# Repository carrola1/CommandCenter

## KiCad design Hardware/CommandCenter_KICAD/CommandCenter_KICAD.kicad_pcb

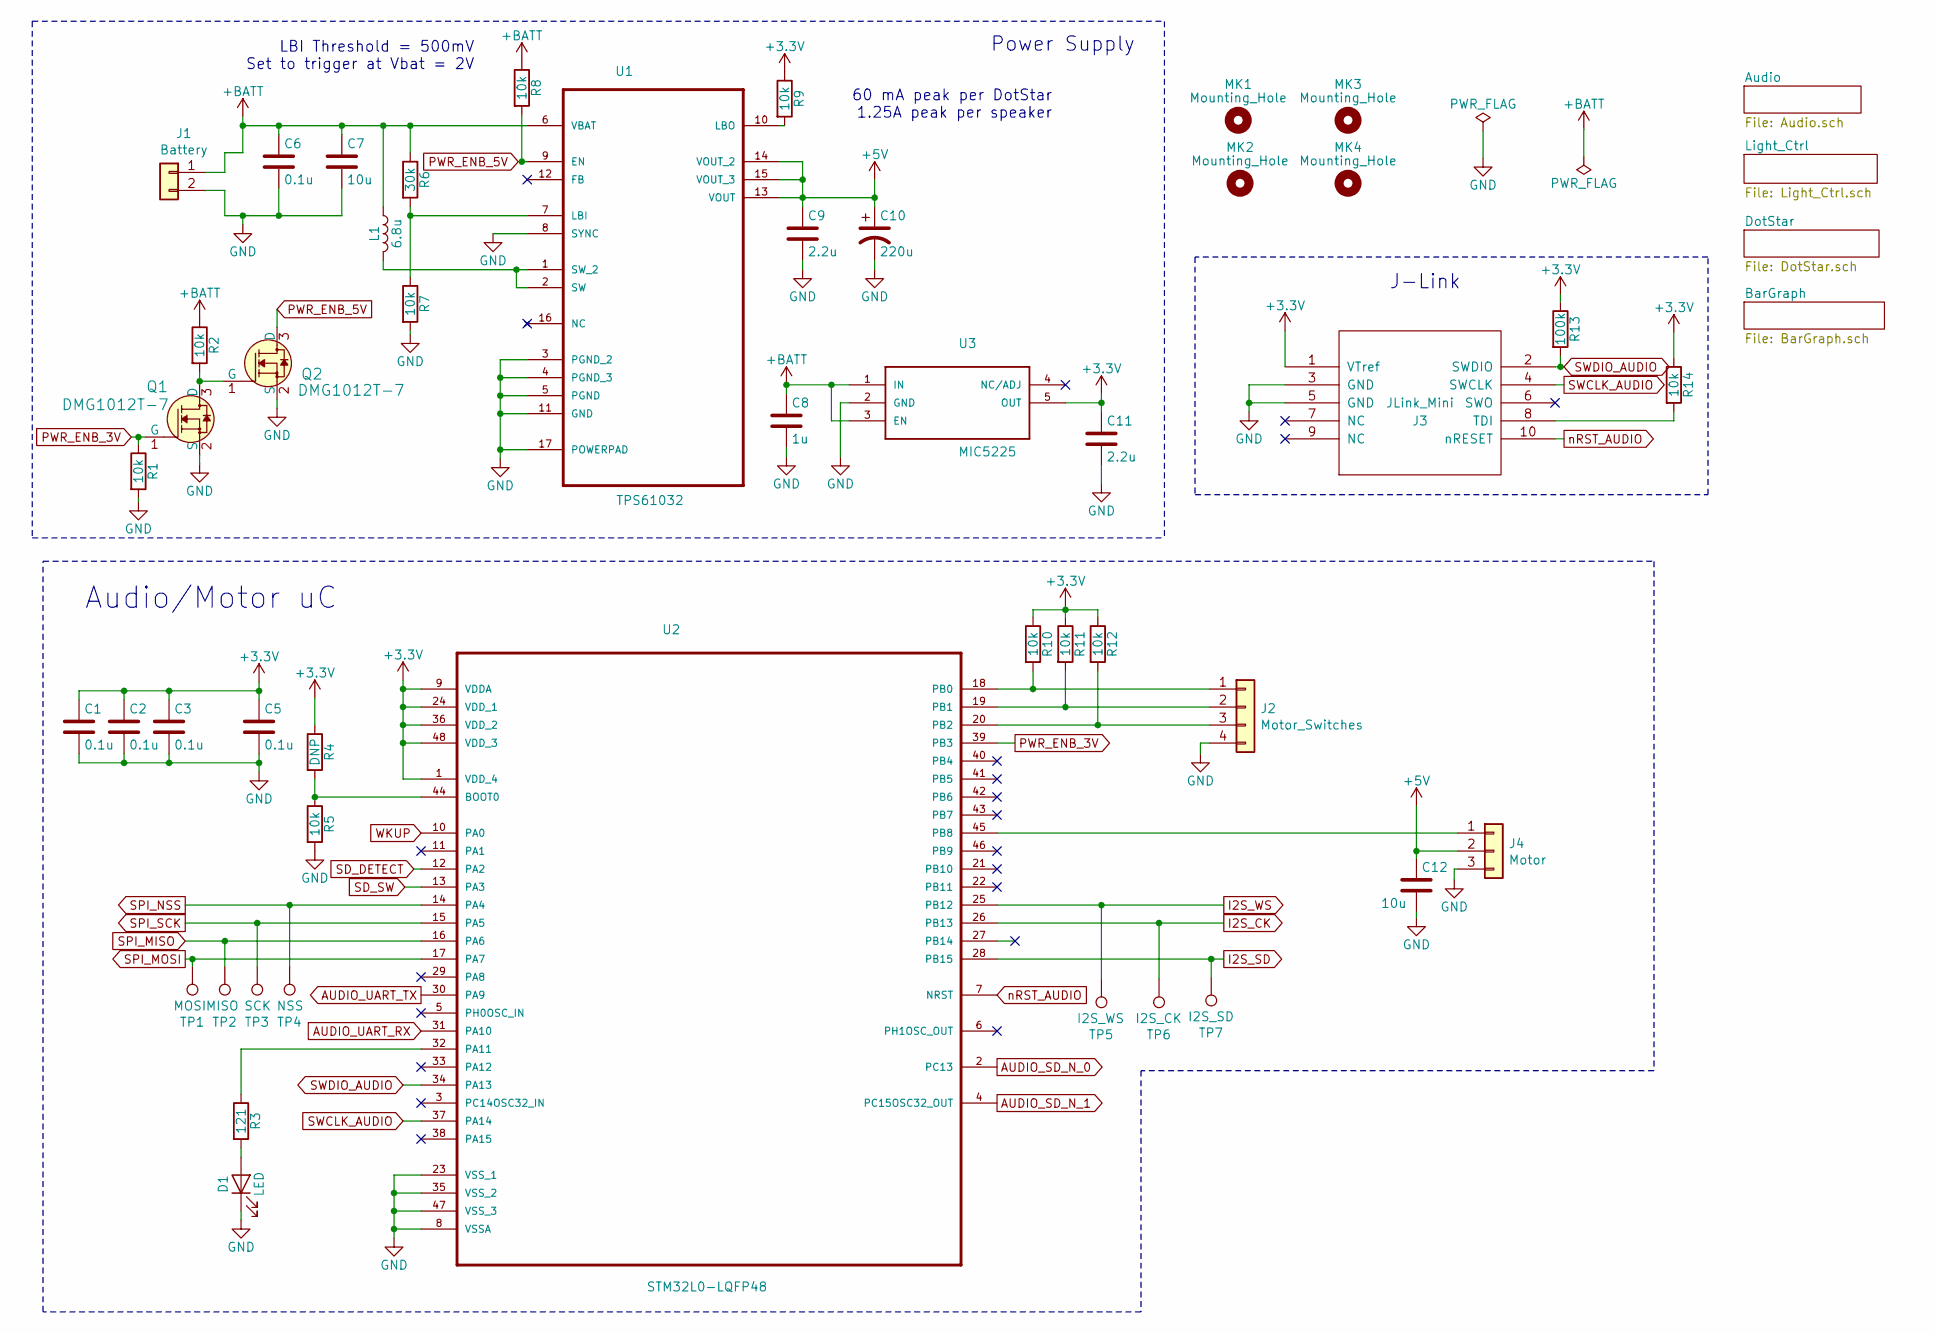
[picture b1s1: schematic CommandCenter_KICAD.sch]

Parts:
C1, C2, C3, C5: 0.1u; C_0603_1608Metric_Pad1.05x0.95mm_HandSolder
C6: 0.1u; C_0402_1005Metric
C7, C12: 10u; C_0603_1608Metric_Pad1.05x0.95mm_HandSolder
C8: 1u; C_0603_1608Metric_Pad1.05x0.95mm_HandSolder
C9, C11: 2.2u; C_0603_1608Metric_Pad1.05x0.95mm_HandSolder
C10: 220u; C_1206_3216Metric_Pad1.42x1.75mm_HandSolder
D1: LED; LED_0603_1608Metric_Pad1.05x0.95mm_HandSolder
J1: Battery; JST_PH_S2B-PH-K_1x02_P2.00mm_Horizontal
J2: Motor_Switches; PinHeader_1x04_P2.54mm_Vertical
J3: JLink_Mini; JLink_Mini_0p05
J4: Motor; PinHeader_1x03_P2.54mm_Vertical
L1: 6.8u; L_12x12mm_H4.5mm
MK1, MK2, MK3, MK4: Mounting_Hole; MountingHole_3.2mm_M3
Q1, Q2: DMG1012T-7; SOT-523; MPN DMG1012T-7; Digi-Key_PN DMG1012T-7DICT-ND
R1, R2, R5, R7, R8, R9, R10, R11, R12, R14: 10k; R_0603_1608Metric_Pad1.05x0.95mm_HandSolder
R3: 121; R_0603_1608Metric_Pad1.05x0.95mm_HandSolder
R4: DNP; R_0603_1608Metric_Pad1.05x0.95mm_HandSolder
R6: 30k; R_0603_1608Metric_Pad1.05x0.95mm_HandSolder
R13: 100k; R_0603_1608Metric_Pad1.05x0.95mm_HandSolder
TP1: MOSI; TestPoint_Pad_2.0x2.0mm
TP2: MISO; TestPoint_Pad_2.0x2.0mm
TP3: SCK; TestPoint_Pad_2.0x2.0mm
TP4: NSS; TestPoint_Pad_2.0x2.0mm
TP5: I2S_WS; TestPoint_Pad_2.0x2.0mm
TP6: I2S_CK; TestPoint_Pad_2.0x2.0mm
TP7: I2S_SD; TestPoint_Pad_2.0x2.0mm
U1: TPS61032; SOP65P640X120-17N
U2: STM32L0-LQFP48; QFP50P900X900X160-48N
U3: MIC5225; SOT-23-5

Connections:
+3V3: C1.1, C2.1, C3.1, C5.1, C11.1, J3.1 (VTref), R4.1, R9.1, R10.1, R11.1, R12.1, R13.1, R14.1, U2.1 (VDD_4), U2.9 (VDDA), U2.24 (VDD_1), U2.36 (VDD_2), U2.48 (VDD_3), U3.5 (OUT); also elsewhere on the board
+5V: C9.1, C10.1, C12.1, J4.2, U1.13 (VOUT), U1.14 (VOUT_2), U1.15 (VOUT_3); also elsewhere on the board
+BATT: C6.1, C7.1, C8.1, J1.1, L1.1, R2.1, R6.1, R8.1, U1.6 (VBAT), U3.1 (IN), U3.3 (EN)
AUDIO_SD_N_0: U2.2 (PC13); also elsewhere on the board
AUDIO_SD_N_1: U2.4 (PC15OSC32_OUT); also elsewhere on the board
AUDIO_UART_RX: U2.31 (PA10); also elsewhere on the board
AUDIO_UART_TX: U2.30 (PA9); also elsewhere on the board
GND: C1.2, C2.2, C3.2, C5.2, C6.2, C7.2, C8.2, C9.2, C10.2, C11.2, C12.2, D1.1 (K), J1.2, J2.4, J3.3 (GND), J3.5 (GND), J4.3, Q1.2 (S), Q2.2 (S), R1.2, R5.2, R7.2, U1.3 (PGND_2), U1.4 (PGND_3), U1.5 (PGND), U1.8 (SYNC), U1.11 (GND), U1.17 (POWERPAD), U2.8 (VSSA), U2.23 (VSS_1), U2.35 (VSS_2), U2.47 (VSS_3), U3.2 (GND); also elsewhere on the board
I2S_CK: TP6.1, U2.26 (PB13); also elsewhere on the board
I2S_SD: TP7.1, U2.28 (PB15); also elsewhere on the board
I2S_WS: TP5.1, U2.25 (PB12); also elsewhere on the board
unnamed: D1.2 (A), R3.2
unnamed: J2.1, R10.2, U2.18 (PB0)
unnamed: J2.2, R11.2, U2.19 (PB1)
unnamed: J2.3, R12.2, U2.20 (PB2)
unnamed: J3.8 (TDI), R14.2
unnamed: J4.1, U2.45 (PB8)
unnamed: L1.2, U1.1 (SW_2), U1.2 (SW)
unnamed: Q1.3 (D), Q2.1 (G), R2.2
unnamed: R3.1, U2.32 (PA11)
unnamed: R4.2, R5.1, U2.44 (BOOT0)
unnamed: R6.2, R7.1, U1.7 (LBI)
unnamed: R9.2, U1.10 (LBO)
PWR_ENB_3V: Q1.1 (G), R1.1, U2.39 (PB3)
PWR_ENB_5V: Q2.3 (D), R8.2, U1.9 (EN)
SD_DETECT: U2.12 (PA2); also elsewhere on the board
SD_SW: U2.13 (PA3); also elsewhere on the board
SPI_MISO: TP2.1, U2.16 (PA6); also elsewhere on the board
SPI_MOSI: TP1.1, U2.17 (PA7); also elsewhere on the board
SPI_NSS: TP4.1, U2.14 (PA4); also elsewhere on the board
SPI_SCK: TP3.1, U2.15 (PA5); also elsewhere on the board
SWCLK_AUDIO: J3.4 (SWCLK), U2.37 (PA14)
SWDIO_AUDIO: J3.2 (SWDIO), R13.2, U2.34 (PA13)
WKUP: U2.10 (PA0); also elsewhere on the board
nRST_AUDIO: J3.10 (nRESET), U2.7 (NRST)

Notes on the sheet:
Power Supply
J-Link
Audio/Motor uC
60 mA peak per DotStar 1.25A peak per speaker
LBI Threshold = 500mV Set to trigger at Vbat = 2V

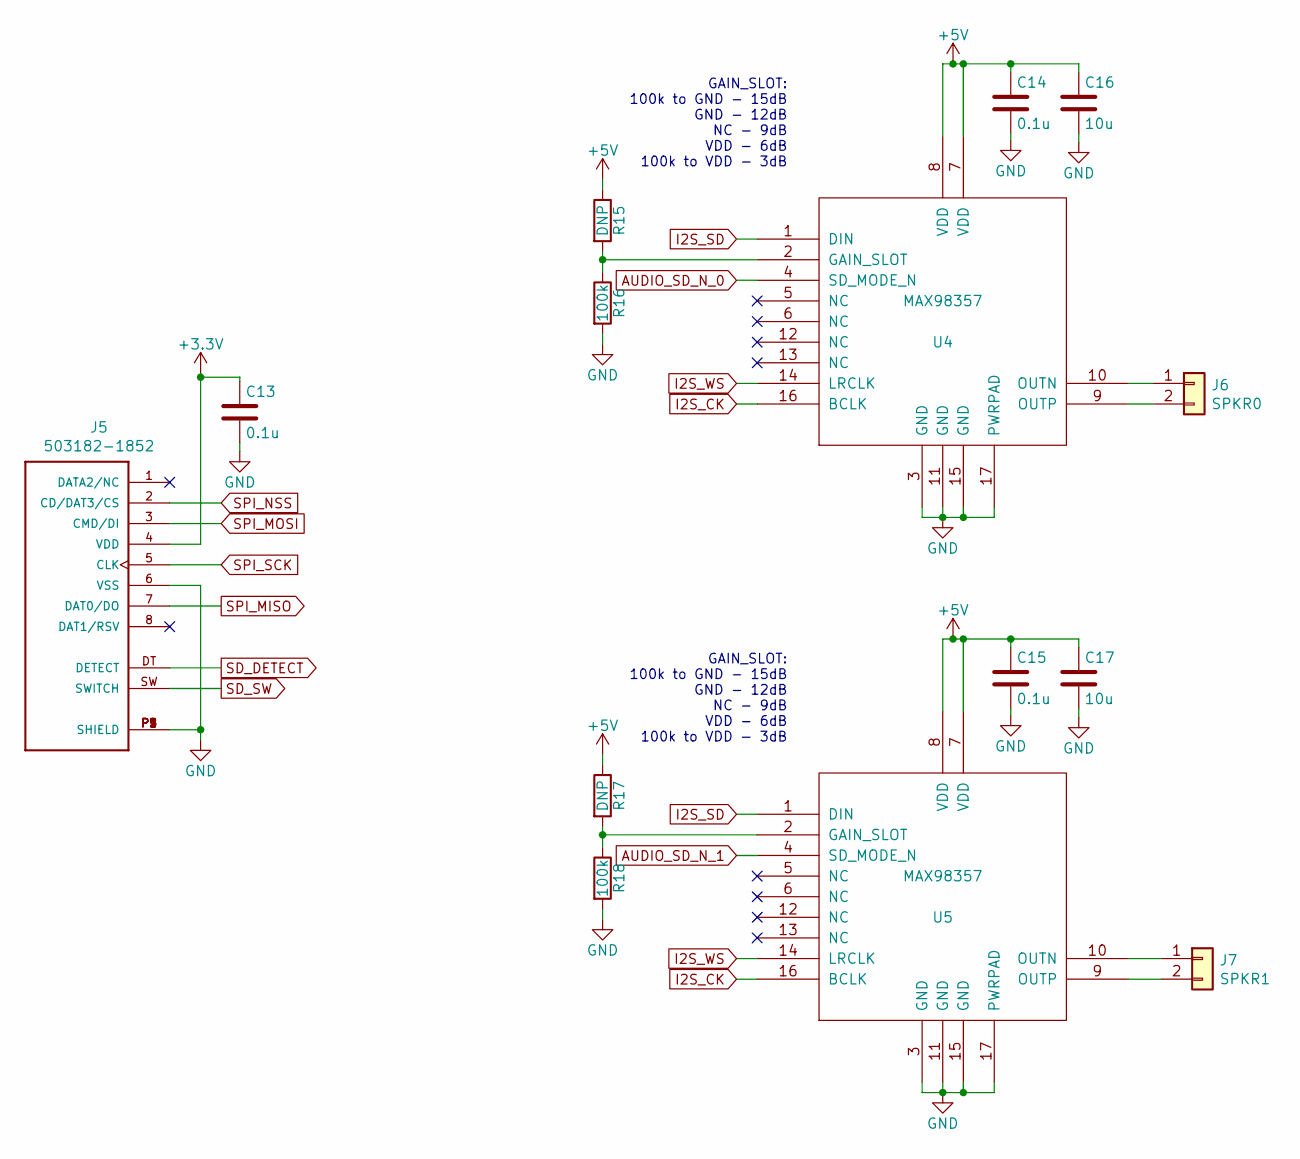
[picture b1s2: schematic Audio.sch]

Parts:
C13, C14, C15: 0.1u; C_0603_1608Metric_Pad1.05x0.95mm_HandSolder
C16, C17: 10u; C_0603_1608Metric_Pad1.05x0.95mm_HandSolder
J5: 503182-1852; MOLEX_503182-1852
J6: SPKR0; PinHeader_1x02_P2.54mm_Vertical
J7: SPKR1; PinHeader_1x02_P2.54mm_Vertical
R15, R17: DNP; R_0603_1608Metric_Pad1.05x0.95mm_HandSolder
R16, R18: 100k; R_0603_1608Metric_Pad1.05x0.95mm_HandSolder
U4, U5: MAX98357; QFN50P300X300X80-17N

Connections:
+3V3: C13.1, J5.4 (VDD); also elsewhere on the board
+5V: C14.1, C15.1, C16.1, C17.1, R15.1, R17.1, U4.7 (VDD), U4.8 (VDD), U5.7 (VDD), U5.8 (VDD); also elsewhere on the board
AUDIO_SD_N_0: U4.4 (SD_MODE_N); also elsewhere on the board
AUDIO_SD_N_1: U5.4 (SD_MODE_N); also elsewhere on the board
GND: C13.2, C14.2, C15.2, C16.2, C17.2, J5.6 (VSS), J5.P1 (SHIELD), J5.P2 (SHIELD), J5.P3 (SHIELD), J5.P4 (SHIELD), J5.P5 (SHIELD), R16.2, R18.2, U4.3 (GND), U4.11 (GND), U4.15 (GND), U4.17 (PWRPAD), U5.3 (GND), U5.11 (GND), U5.15 (GND), U5.17 (PWRPAD); also elsewhere on the board
I2S_CK: U4.16 (BCLK), U5.16 (BCLK); also elsewhere on the board
I2S_SD: U4.1 (DIN), U5.1 (DIN); also elsewhere on the board
I2S_WS: U4.14 (LRCLK), U5.14 (LRCLK); also elsewhere on the board
unnamed: J6.1, U4.10 (OUTN)
unnamed: J6.2, U4.9 (OUTP)
unnamed: J7.1, U5.10 (OUTN)
unnamed: J7.2, U5.9 (OUTP)
unnamed: R15.2, R16.1, U4.2 (GAIN_SLOT)
unnamed: R17.2, R18.1, U5.2 (GAIN_SLOT)
SD_DETECT: J5.DT (DETECT); also elsewhere on the board
SD_SW: J5.SW (SWITCH); also elsewhere on the board
SPI_MISO: J5.7 (DAT0/DO); also elsewhere on the board
SPI_MOSI: J5.3 (CMD/DI); also elsewhere on the board
SPI_NSS: J5.2 (CD/DAT3/CS); also elsewhere on the board
SPI_SCK: J5.5 (CLK); also elsewhere on the board

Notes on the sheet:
GAIN_SLOT: 100k to GND - 15dB GND - 12dB NC - 9dB VDD - 6dB 100k to VDD - 3dB

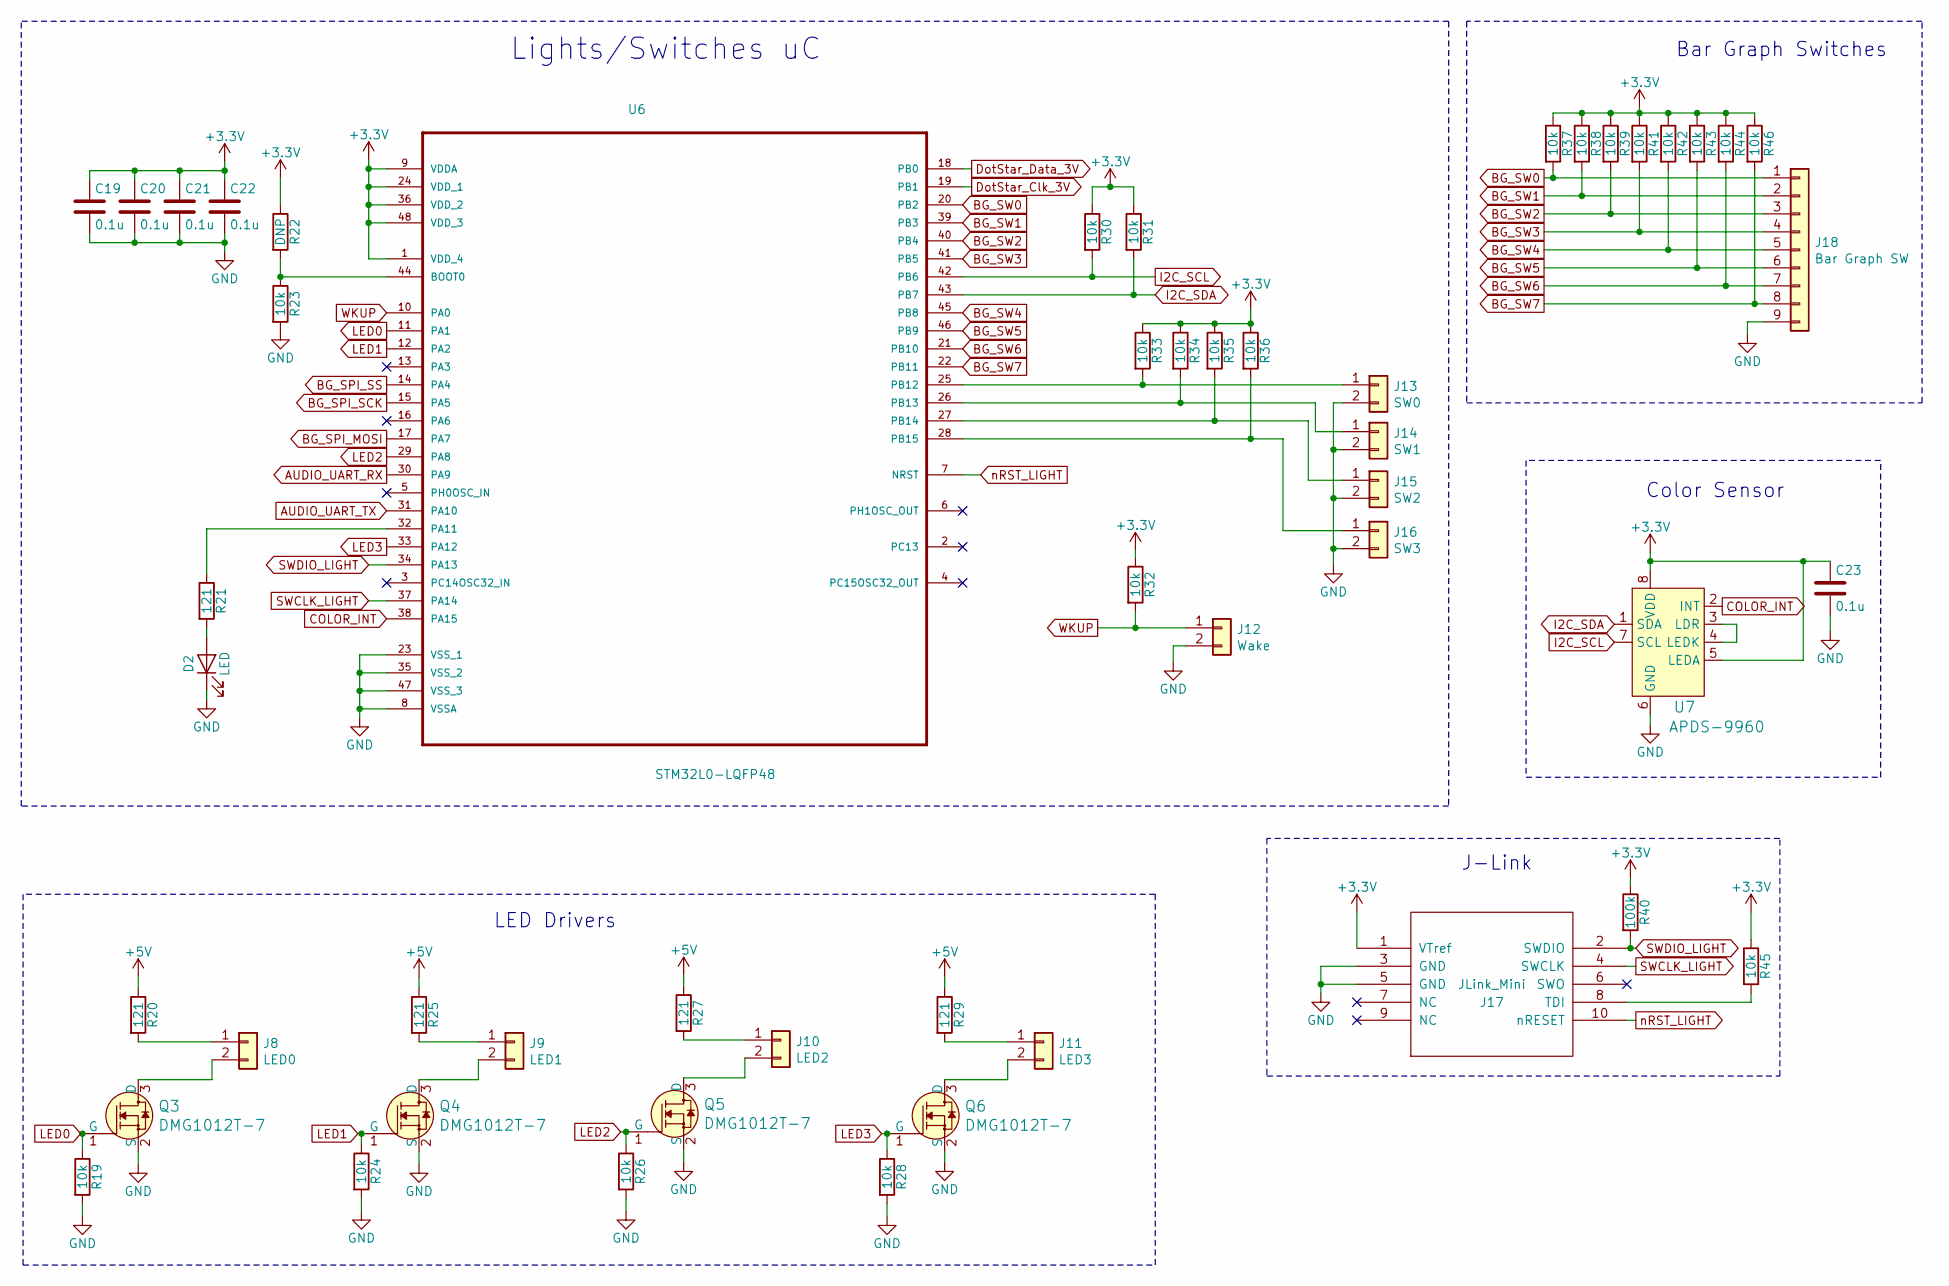
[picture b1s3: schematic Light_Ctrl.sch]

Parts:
C19, C20, C21, C22, C23: 0.1u; C_0603_1608Metric_Pad1.05x0.95mm_HandSolder
D2: LED; LED_0603_1608Metric_Pad1.05x0.95mm_HandSolder
J8: LED0; PinHeader_1x02_P2.54mm_Vertical
J9: LED1; PinHeader_1x02_P2.54mm_Vertical
J10: LED2; PinHeader_1x02_P2.54mm_Vertical
J11: LED3; PinHeader_1x02_P2.54mm_Vertical
J12: Wake; PinHeader_1x02_P2.54mm_Vertical
J13: SW0; PinHeader_1x02_P2.54mm_Vertical
J14: SW1; PinHeader_1x02_P2.54mm_Vertical
J15: SW2; PinHeader_1x02_P2.54mm_Vertical
J16: SW3; PinHeader_1x02_P2.54mm_Vertical
J17: JLink_Mini; JLink_Mini_0p05
J18: Bar Graph SW; PinHeader_1x09_P2.54mm_Vertical
Q3, Q4, Q5, Q6: DMG1012T-7; SOT-523; MPN DMG1012T-7; Digi-Key_PN DMG1012T-7DICT-ND
R19, R23, R24, R26, R28, R30, R31, R32, R33, R34, R35, R36, R37, R38, R39, R41, R42, R43, R44, R45, R46: 10k; R_0603_1608Metric_Pad1.05x0.95mm_HandSolder
R20, R21, R25, R27, R29: 121; R_0603_1608Metric_Pad1.05x0.95mm_HandSolder
R22: DNP; R_0603_1608Metric_Pad1.05x0.95mm_HandSolder
R40: 100k; R_0603_1608Metric_Pad1.05x0.95mm_HandSolder
U6: STM32L0-LQFP48; QFP50P900X900X160-48N
U7: APDS-9960; Ambient_Prox_APDS-9960; MPN APDS-9960; Digi-Key_PN 516-3480-1-ND

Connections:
+3V3: C19.1, C20.1, C21.1, C22.1, C23.1, J17.1 (VTref), R22.1, R30.1, R31.1, R32.1, R33.1, R34.1, R35.1, R36.1, R37.1, R38.1, R39.1, R40.1, R41.1, R42.1, R43.1, R44.1, R45.1, R46.1, U6.1 (VDD_4), U6.9 (VDDA), U6.24 (VDD_1), U6.36 (VDD_2), U6.48 (VDD_3), U7.5 (LEDA), U7.8 (VDD); also elsewhere on the board
+5V: R20.1, R25.1, R27.1, R29.1; also elsewhere on the board
AUDIO_UART_RX: U6.30 (PA9); also elsewhere on the board
AUDIO_UART_TX: U6.31 (PA10); also elsewhere on the board
BG_SPI_MOSI: U6.17 (PA7); also elsewhere on the board
BG_SPI_SCK: U6.15 (PA5); also elsewhere on the board
BG_SPI_SS: U6.14 (PA4); also elsewhere on the board
BG_SW0: J18.1, R37.2, U6.20 (PB2)
BG_SW1: J18.2, R38.2, U6.39 (PB3)
BG_SW2: J18.3, R39.2, U6.40 (PB4)
BG_SW3: J18.4, R41.2, U6.41 (PB5)
BG_SW4: J18.5, R42.2, U6.45 (PB8)
BG_SW5: J18.6, R43.2, U6.46 (PB9)
BG_SW6: J18.7, R44.2, U6.21 (PB10)
BG_SW7: J18.8, R46.2, U6.22 (PB11)
COLOR_INT: U6.38 (PA15), U7.2 (INT)
DotStar_Clk_3V: U6.19 (PB1); also elsewhere on the board
DotStar_Data_3V: U6.18 (PB0); also elsewhere on the board
GND: C19.2, C20.2, C21.2, C22.2, C23.2, D2.1 (K), J12.2, J13.2, J14.2, J15.2, J16.2, J17.3 (GND), J17.5 (GND), J18.9, Q3.2 (S), Q4.2 (S), Q5.2 (S), Q6.2 (S), R19.2, R23.2, R24.2, R26.2, R28.2, U6.8 (VSSA), U6.23 (VSS_1), U6.35 (VSS_2), U6.47 (VSS_3), U7.6 (GND); also elsewhere on the board
I2C_SCL: R30.2, U6.42 (PB6), U7.7 (SCL)
I2C_SDA: R31.2, U6.43 (PB7), U7.1 (SDA)
LED0: Q3.1 (G), R19.1, U6.11 (PA1)
LED1: Q4.1 (G), R24.1, U6.12 (PA2)
LED2: Q5.1 (G), R26.1, U6.29 (PA8)
LED3: Q6.1 (G), R28.1, U6.33 (PA12)
unnamed: D2.2 (A), R21.2
unnamed: J8.1, R20.2
unnamed: J8.2, Q3.3 (D)
unnamed: J9.1, R25.2
unnamed: J9.2, Q4.3 (D)
unnamed: J10.1, R27.2
unnamed: J10.2, Q5.3 (D)
unnamed: J11.1, R29.2
unnamed: J11.2, Q6.3 (D)
unnamed: J13.1, R33.2, U6.25 (PB12)
unnamed: J14.1, R34.2, U6.26 (PB13)
unnamed: J15.1, R35.2, U6.27 (PB14)
unnamed: J16.1, R36.2, U6.28 (PB15)
unnamed: J17.8 (TDI), R45.2
unnamed: R21.1, U6.32 (PA11)
unnamed: R22.2, R23.1, U6.44 (BOOT0)
unnamed: U7.3 (LDR), U7.4 (LEDK)
SWCLK_LIGHT: J17.4 (SWCLK), U6.37 (PA14)
SWDIO_LIGHT: J17.2 (SWDIO), R40.2, U6.34 (PA13)
WKUP: J12.1, R32.2, U6.10 (PA0); also elsewhere on the board
nRST_LIGHT: J17.10 (nRESET), U6.7 (NRST)

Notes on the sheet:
Lights/Switches uC
J-Link
LED Drivers
Color Sensor
Bar Graph Switches

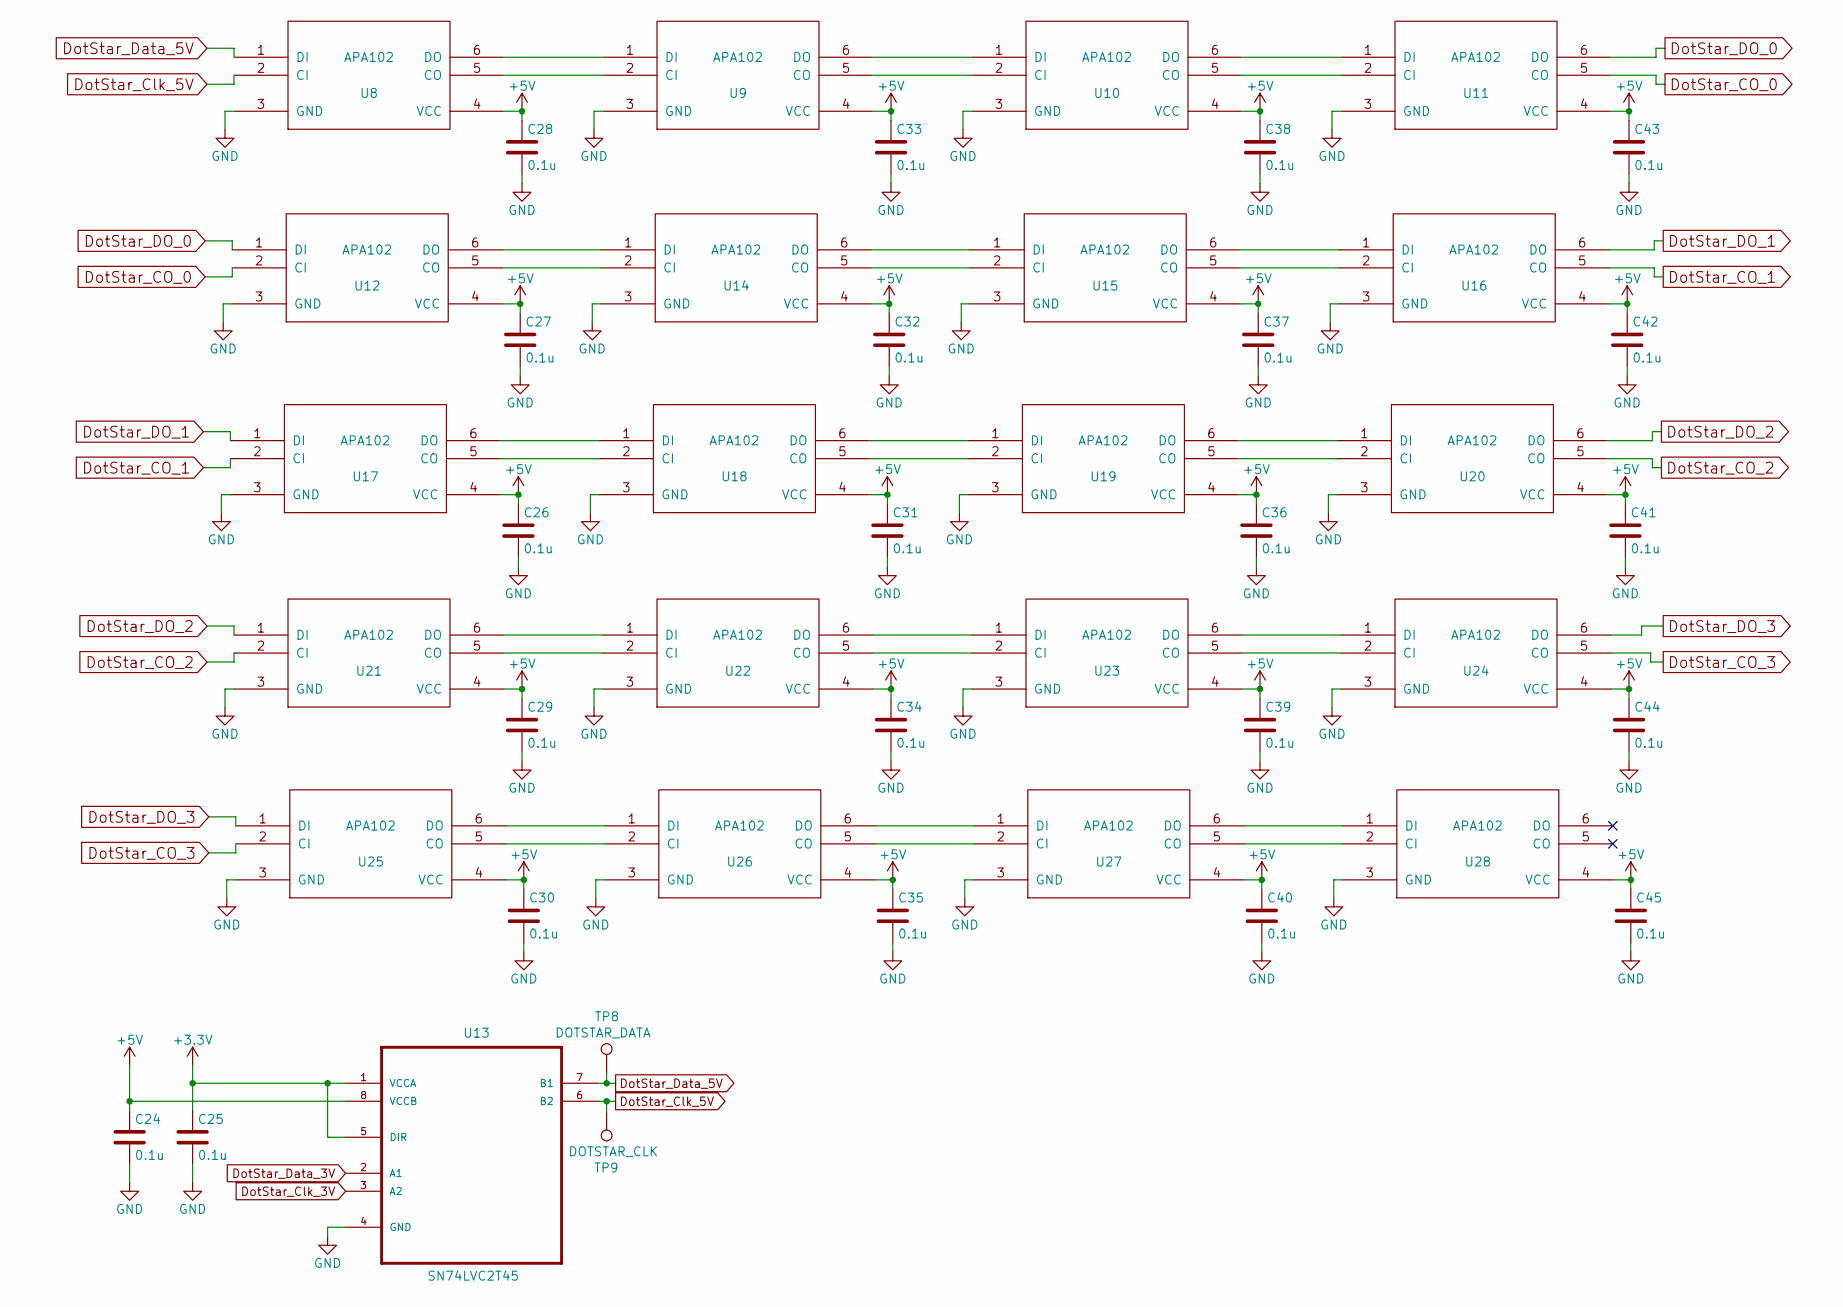
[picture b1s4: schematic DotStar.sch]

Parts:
C24, C25, C26, C27, C28, C29, C30, C31, C32, C33, C34, C35, C36, C37, C38, C39, C40, C41, C42, C43, C44, C45: 0.1u; C_0603_1608Metric_Pad1.05x0.95mm_HandSolder
TP8: DOTSTAR_DATA; TestPoint_Pad_2.0x2.0mm
TP9: DOTSTAR_CLK; TestPoint_Pad_2.0x2.0mm
U8, U9, U10, U11, U12, U14, U15, U16, U17, U18, U19, U20, U21, U22, U23, U24, U25, U26, U27, U28: APA102; APA102_hand_solder
U13: SN74LVC2T45; SOP50P310X90-8N

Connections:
+3V3: C25.1, U13.1 (VCCA), U13.5 (DIR); also elsewhere on the board
+5V: C24.1, C26.1, C27.1, C28.1, C29.1, C30.1, C31.1, C32.1, C33.1, C34.1, C35.1, C36.1, C37.1, C38.1, C39.1, C40.1, C41.1, C42.1, C43.1, C44.1, C45.1, U8.4 (VCC), U9.4 (VCC), U10.4 (VCC), U11.4 (VCC), U12.4 (VCC), U13.8 (VCCB), U14.4 (VCC), U15.4 (VCC), U16.4 (VCC), U17.4 (VCC), U18.4 (VCC), U19.4 (VCC), U20.4 (VCC), U21.4 (VCC), U22.4 (VCC), U23.4 (VCC), U24.4 (VCC), U25.4 (VCC), U26.4 (VCC), U27.4 (VCC), U28.4 (VCC); also elsewhere on the board
DotStar_CO_0: U11.5 (CO), U12.2 (CI)
DotStar_CO_1: U16.5 (CO), U17.2 (CI)
DotStar_CO_2: U20.5 (CO), U21.2 (CI)
DotStar_CO_3: U24.5 (CO), U25.2 (CI)
DotStar_Clk_3V: U13.3 (A2); also elsewhere on the board
DotStar_Clk_5V: TP9.1, U8.2 (CI), U13.6 (B2)
DotStar_DO_0: U11.6 (DO), U12.1 (DI)
DotStar_DO_1: U16.6 (DO), U17.1 (DI)
DotStar_DO_2: U20.6 (DO), U21.1 (DI)
DotStar_DO_3: U24.6 (DO), U25.1 (DI)
DotStar_Data_3V: U13.2 (A1); also elsewhere on the board
DotStar_Data_5V: TP8.1, U8.1 (DI), U13.7 (B1)
GND: C24.2, C25.2, C26.2, C27.2, C28.2, C29.2, C30.2, C31.2, C32.2, C33.2, C34.2, C35.2, C36.2, C37.2, C38.2, C39.2, C40.2, C41.2, C42.2, C43.2, C44.2, C45.2, U8.3 (GND), U9.3 (GND), U10.3 (GND), U11.3 (GND), U12.3 (GND), U13.4 (GND), U14.3 (GND), U15.3 (GND), U16.3 (GND), U17.3 (GND), U18.3 (GND), U19.3 (GND), U20.3 (GND), U21.3 (GND), U22.3 (GND), U23.3 (GND), U24.3 (GND), U25.3 (GND), U26.3 (GND), U27.3 (GND), U28.3 (GND); also elsewhere on the board
unnamed: U8.5 (CO), U9.2 (CI)
unnamed: U8.6 (DO), U9.1 (DI)
unnamed: U9.6 (DO), U10.1 (DI)
unnamed: U9.5 (CO), U10.2 (CI)
unnamed: U10.5 (CO), U11.2 (CI)
unnamed: U10.6 (DO), U11.1 (DI)
unnamed: U12.5 (CO), U14.2 (CI)
unnamed: U12.6 (DO), U14.1 (DI)
unnamed: U14.5 (CO), U15.2 (CI)
unnamed: U14.6 (DO), U15.1 (DI)
unnamed: U15.5 (CO), U16.2 (CI)
unnamed: U15.6 (DO), U16.1 (DI)
unnamed: U17.5 (CO), U18.2 (CI)
unnamed: U17.6 (DO), U18.1 (DI)
unnamed: U18.5 (CO), U19.2 (CI)
unnamed: U18.6 (DO), U19.1 (DI)
unnamed: U19.5 (CO), U20.2 (CI)
unnamed: U19.6 (DO), U20.1 (DI)
unnamed: U21.5 (CO), U22.2 (CI)
unnamed: U21.6 (DO), U22.1 (DI)
unnamed: U22.5 (CO), U23.2 (CI)
unnamed: U22.6 (DO), U23.1 (DI)
unnamed: U23.5 (CO), U24.2 (CI)
unnamed: U23.6 (DO), U24.1 (DI)
unnamed: U25.5 (CO), U26.2 (CI)
unnamed: U25.6 (DO), U26.1 (DI)
unnamed: U26.5 (CO), U27.2 (CI)
unnamed: U26.6 (DO), U27.1 (DI)
unnamed: U27.5 (CO), U28.2 (CI)
unnamed: U27.6 (DO), U28.1 (DI)

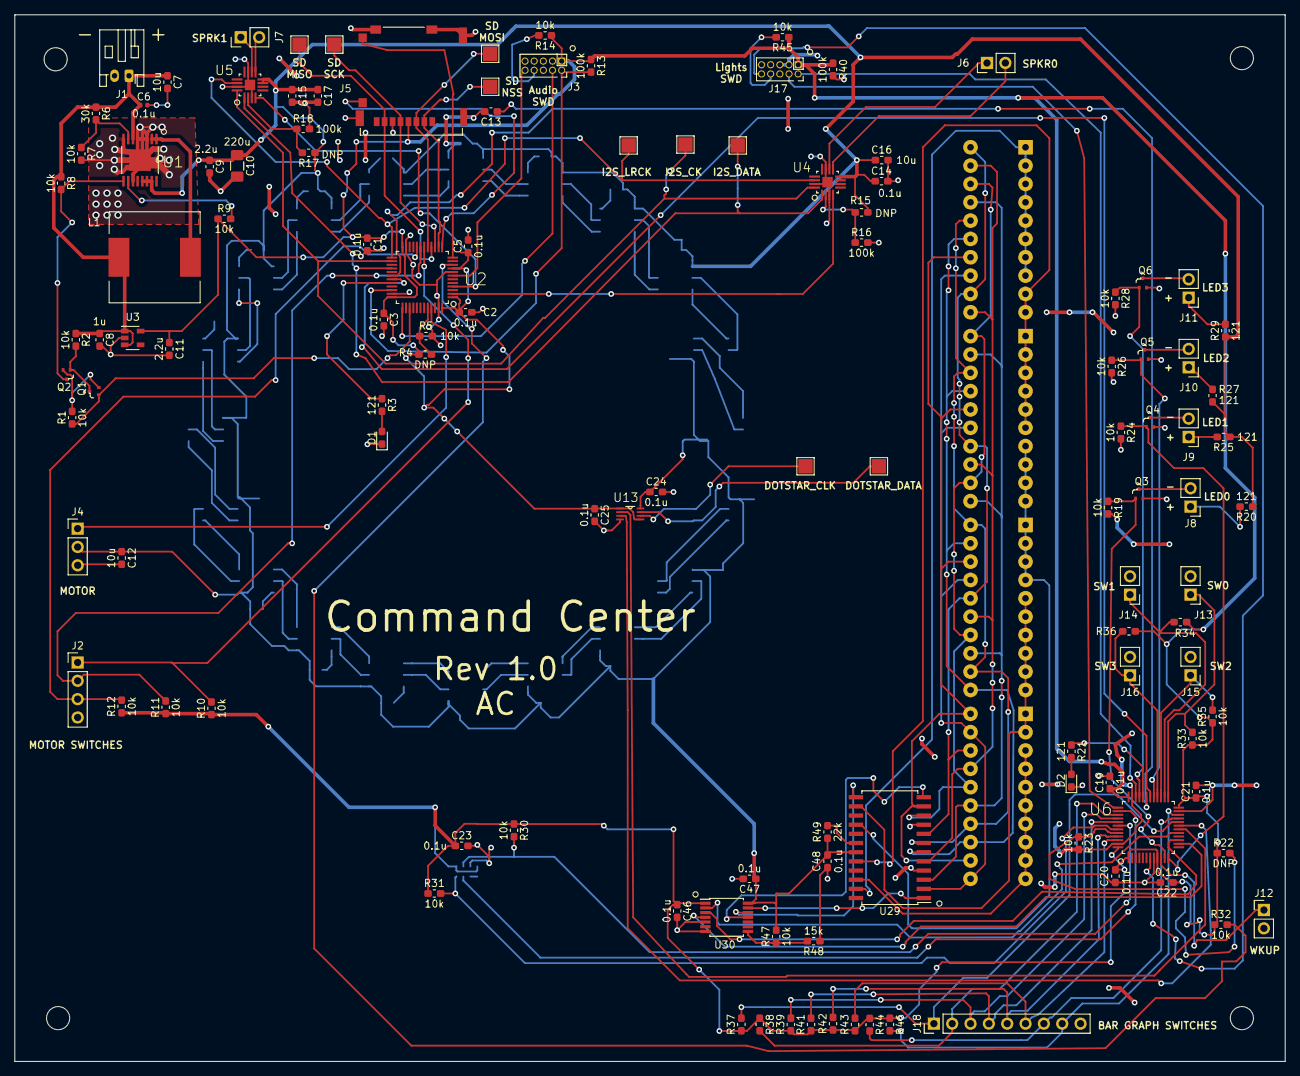
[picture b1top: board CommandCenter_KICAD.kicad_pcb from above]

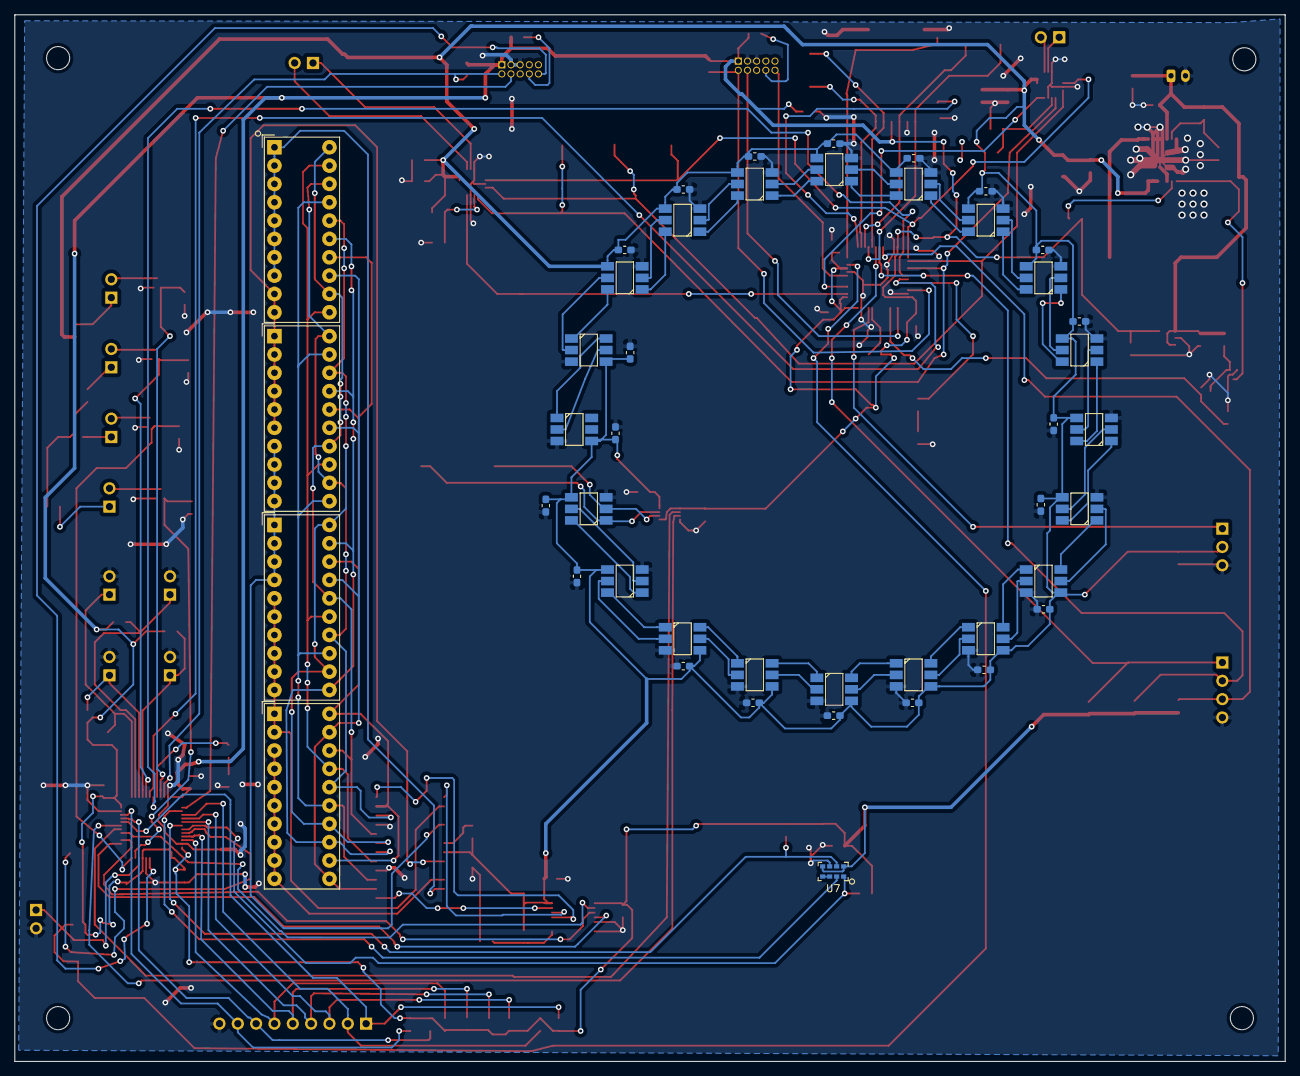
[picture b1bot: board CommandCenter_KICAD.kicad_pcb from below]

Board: 2 copper layers, 176.0 x 145.0 mm, 169 parts (45 on the bottom side), 139 nets.

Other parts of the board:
BAR1, BAR2, BAR3, BAR4: HDSP-4830_2; HDSP-4830
C46, C47, C48: 0.1u; C_0603_1608Metric_Pad1.05x0.95mm_HandSolder
MKe: Mounting_Hole; MountingHole_3.2mm_M3
R47: 10k; R_0603_1608Metric_Pad1.05x0.95mm_HandSolder
R48: 15k; R_0603_1608Metric_Pad1.05x0.95mm_HandSolder
R49: 22k; R_0603_1608Metric_Pad1.05x0.95mm_HandSolder
U29: MAX7219; SOIC-24W_7.5x15.4mm_P1.27mm
U30: TXB0104PW; TSSOP-14_4.4x5mm_P0.65mm

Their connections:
+3V3: C46.1, U30.1; also elsewhere on the board
+5V: C47.1, C48.1, R47.2, R49.1, U29.19, U30.14; also elsewhere on the board
BG_SPI_MOSI: U30.2; also elsewhere on the board
BG_SPI_MOSI_5V: U29.1, U30.13
BG_SPI_SCK: U30.3; also elsewhere on the board
BG_SPI_SCK_5V: U29.13, U30.12
BG_SPI_SS: U30.4; also elsewhere on the board
BG_SPI_SS_5V: U29.12, U30.11
DIG0: BAR1.13, BAR2.15, BAR3.17, BAR4.11, BAR4.19, U29.2
DIG1: BAR1.14, BAR2.16, BAR3.18, BAR4.12, BAR4.20, U29.11
DIG2: BAR1.15, BAR2.17, BAR3.11, BAR3.19, BAR4.13, U29.6
DIG3: BAR1.16, BAR2.18, BAR3.12, BAR3.20, BAR4.14, U29.7
DIG4: BAR1.17, BAR2.11, BAR2.19, BAR3.13, BAR4.15, U29.3
DIG5: BAR1.18, BAR2.12, BAR2.20, BAR3.14, BAR4.16, U29.10
DIG6: BAR1.11, BAR1.19, BAR2.13, BAR3.15, BAR4.17, U29.5
DIG7: BAR1.12, BAR1.20, BAR2.14, BAR3.16, BAR4.18, U29.8
GND: C46.2, C47.2, C48.2, R48.1, U29.4, U29.9, U30.5, U30.7; also elsewhere on the board
unnamed: R47.1, R48.2, U30.8
unnamed: R49.2, U29.18
SEG_A: BAR3.5, BAR3.6, BAR3.7, BAR3.8, BAR3.9, BAR3.10, BAR4.1, BAR4.2, U29.14
SEG_B: BAR2.7, BAR2.8, BAR2.9, BAR2.10, BAR3.1, BAR3.2, BAR3.3, BAR3.4, U29.16
SEG_C: BAR1.9, BAR1.10, BAR2.1, BAR2.2, BAR2.3, BAR2.4, BAR2.5, BAR2.6, U29.20
SEG_D: BAR1.1, BAR1.2, BAR1.3, BAR1.4, BAR1.5, BAR1.6, BAR1.7, BAR1.8, U29.23
SEG_DP: BAR4.3, BAR4.4, BAR4.5, BAR4.6, BAR4.7, BAR4.8, BAR4.9, BAR4.10, U29.22

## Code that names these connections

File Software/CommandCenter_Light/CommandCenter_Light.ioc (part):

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Mcu.Name=STM32L052C(6-8)Tx
Mcu.Package=LQFP48
Mcu.UserName=STM32L052C8Tx
PA0.Mode=SYS_WakeUp0
PA0.Signal=SYS_WKUP1
PA1.GPIOParameters=GPIO_Label
PA1.GPIO_Label=LED_0
PA1.Signal=GPIO_Output
PA10.Mode=Asynchronous
PA10.Signal=USART1_RX
PA11.GPIOParameters=GPIO_Label
PA11.GPIO_Label=TEST_LED
PA11.Signal=GPIO_Output
PA12.GPIOParameters=GPIO_Label
PA12.GPIO_Label=LED_3
PA12.Signal=GPIO_Output
PA13.Mode=Serial_Wire
PA13.Signal=SYS_SWDIO
PA14.Mode=Serial_Wire
PA14.Signal=SYS_SWCLK
PA15.GPIOParameters=GPIO_Label
PA15.GPIO_Label=COLOR_INT
PA15.Signal=GPIO_Input
PA2.GPIOParameters=GPIO_Label
PA2.GPIO_Label=LED_1
PA2.Signal=GPIO_Output
PA4.GPIOParameters=PinState,GPIO_Label
PA4.GPIO_Label=SPI_SS
PA4.PinState=GPIO_PIN_SET
PA4.Signal=GPIO_Output
PA5.GPIOParameters=GPIO_PuPd
PA5.GPIO_PuPd=GPIO_NOPULL
PA5.Mode=TX_Only_Simplex_Unidirect_Master
PA5.Signal=SPI1_SCK
PA6.Signal=SPI1_MISO
PA7.GPIOParameters=GPIO_PuPd
PA7.GPIO_PuPd=GPIO_NOPULL
PA7.Mode=TX_Only_Simplex_Unidirect_Master
PA7.Signal=SPI1_MOSI
PA8.GPIOParameters=GPIO_Label
PA8.GPIO_Label=LED_2
PA8.Signal=GPIO_Output
PA9.Mode=Asynchronous
PA9.Signal=USART1_TX
PB0.GPIOParameters=GPIO_Label
PB0.GPIO_Label=DOTSTAR_DATA
PB0.Signal=GPIO_Output
PB1.GPIOParameters=GPIO_Label
PB1.GPIO_Label=DOTSTAR_CLK
PB1.Signal=GPIO_Output
PB10.GPIOParameters=GPIO_Label
PB10.GPIO_Label=BG_SW_6
PB10.Signal=GPIO_Input
PB11.GPIOParameters=GPIO_Label
PB11.GPIO_Label=BG_SW_7
PB11.Signal=GPIO_Input
PB12.GPIOParameters=GPIO_Label
PB12.GPIO_Label=SW_0
PB12.Signal=GPIO_Input
PB13.GPIOParameters=GPIO_Label
PB13.GPIO_Label=SW_1
PB13.Signal=GPIO_Input
PB14.GPIOParameters=GPIO_Label
PB14.GPIO_Label=SW_2
PB14.Signal=GPIO_Input
PB15.GPIOParameters=GPIO_Label
PB15.GPIO_Label=SW_3
PB15.Signal=GPIO_Input
PB2.GPIOParameters=GPIO_Label
PB2.GPIO_Label=BG_SW_0
PB2.Signal=GPIO_Input
PB3.GPIOParameters=GPIO_Label
PB3.GPIO_Label=BG_SW_1
PB3.Signal=GPIO_Input
PB4.GPIOParameters=GPIO_Label
PB4.GPIO_Label=BG_SW_2
PB4.Signal=GPIO_Input
PB5.GPIOParameters=GPIO_Label
PB5.GPIO_Label=BG_SW_3
PB5.Signal=GPIO_Input
PB6.GPIOParameters=GPIO_PuPdOD
PB6.GPIO_PuPdOD=GPIO_NOPULL
PB6.Mode=I2C
PB6.Signal=I2C1_SCL
PB7.Mode=I2C
PB7.Signal=I2C1_SDA
PB8.GPIOParameters=GPIO_Label
PB8.GPIO_Label=BG_SW_4
PB8.Signal=GPIO_Input
PB9.GPIOParameters=GPIO_Label
PB9.GPIO_Label=BG_SW_5
PB9.Signal=GPIO_Input
RCC.HSE_VALUE=8000000
RCC.SYSCLKFreq_VALUE=32000000
RCC.SYSCLKSource=RCC_SYSCLKSOURCE_PLLCLK
board=custom

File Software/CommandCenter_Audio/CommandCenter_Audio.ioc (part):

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Mcu.Name=STM32L052C(6-8)Tx
Mcu.Package=LQFP48
Mcu.UserName=STM32L052C8Tx
PA0.Mode=SYS_WakeUp0
PA0.Signal=SYS_WKUP1
PA10.Mode=Asynchronous
PA10.Signal=USART1_RX
PA11.GPIOParameters=GPIO_Label
PA11.GPIO_Label=TEST_LED
PA11.Signal=GPIO_Output
PA13.Mode=Serial_Wire
PA13.Signal=SYS_SWDIO
PA14.Mode=Serial_Wire
PA14.Signal=SYS_SWCLK
PA2.GPIOParameters=GPIO_Label
PA2.GPIO_Label=SD_DETECT
PA2.Signal=GPIO_Input
PA3.GPIOParameters=GPIO_Label
PA3.GPIO_Label=SD_SW
PA3.Signal=GPIO_Input
PA4.Signal=SPI1_NSS
PA5.Mode=Full_Duplex_Master
PA5.Signal=SPI1_SCK
PA6.Mode=Full_Duplex_Master
PA6.Signal=SPI1_MISO
PA7.Mode=Full_Duplex_Master
PA7.Signal=SPI1_MOSI
PA9.Mode=Asynchronous
PA9.Signal=USART1_TX
PB0.GPIOParameters=GPIO_Label
PB0.GPIO_Label=MOTOR_SW_0
PB0.Signal=GPIO_Input
PB1.GPIOParameters=GPIO_Label
PB1.GPIO_Label=MOTOR_SW_1
PB1.Signal=GPIO_Input
PB12.Mode=Half_Duplex_Master
PB12.Signal=I2S2_WS
PB13.Mode=Half_Duplex_Master
PB13.Signal=I2S2_CK
PB15.Mode=Half_Duplex_Master
PB15.Signal=I2S2_SD
PB2.GPIOParameters=GPIO_Label
PB2.GPIO_Label=MOTOR_CTRL
PB2.Mode=WaveformGeneration
PB2.Signal=LPTIM1_OUT
PB3.GPIOParameters=GPIO_Label
PB3.GPIO_Label=PWR_ENB
PB3.Signal=GPIO_Output
PB8.GPIOParameters=GPIO_Label
PB8.GPIO_Label=MOTOR_SW_2
PB8.Signal=GPIO_Input
PC13.GPIOParameters=GPIO_Label
PC13.GPIO_Label=AUDIO_SD_N_0
PC13.Signal=GPIO_Output
PC15-OSC32_OUT.GPIOParameters=GPIO_Label
PC15-OSC32_OUT.GPIO_Label=AUDIO_SD_N_1
PC15-OSC32_OUT.Signal=GPIO_Output
RCC.HSE_VALUE=8000000
RCC.SYSCLKFreq_VALUE=32000000
RCC.SYSCLKSource=RCC_SYSCLKSOURCE_PLLCLK
board=custom

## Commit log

2019-04-29 Started PCB Schematic
2019-05-12 Layout started
2019-08-28 Light Project Stable
    DotStars and bar graph working. Getting master read nack on I2C to color sensor.
2019-09-02 Bar graph and color sensor working
2019-09-11 Audio project working again
    Had to recreate STM32IDE project to get code to load. Not sure what fixed it. Audio amps were not initially working. Fixed by changing compile optimization from "None" to "Optimize for Size". This wa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
2019-10-16 Servo motor functioning.
2019-10-23 Progress toward final implementation
2019-10-23 UART Working
2019-10-28 All hardware functional
    Sounds added for switch inputs.
2019-12-28 Adding color detection and new audio files.
2019-12-28 Added color detect filtering and RNG for asking to find a random color.
2019-12-28 Added color found success/fail with audio triggers.
2019-12-31 Wake/sleep key switch functionality added.
2020-01-03 Minor timing changes.
2020-01-03 Audio controller now provides UART feedback for when audio is playing
2020-01-03 Final release before mounting
2020-01-06 Added calibration routine on startup
2020-01-07 Fixed audio distortion
    Secret was to change GPIO speed of I2S signals.
2020-02-09 Reduced volume
2020-03-23 Updated to play song even if color is wrong
2020-03-31 Re-architected software
    Re-wrote code to use state machines. Cleaned up variable names. Moved common code blocks to functions. Updated audio to play in chunks, allowing the process to be interrupted.
2020-04-01 Added audio finished message from audio controller.
